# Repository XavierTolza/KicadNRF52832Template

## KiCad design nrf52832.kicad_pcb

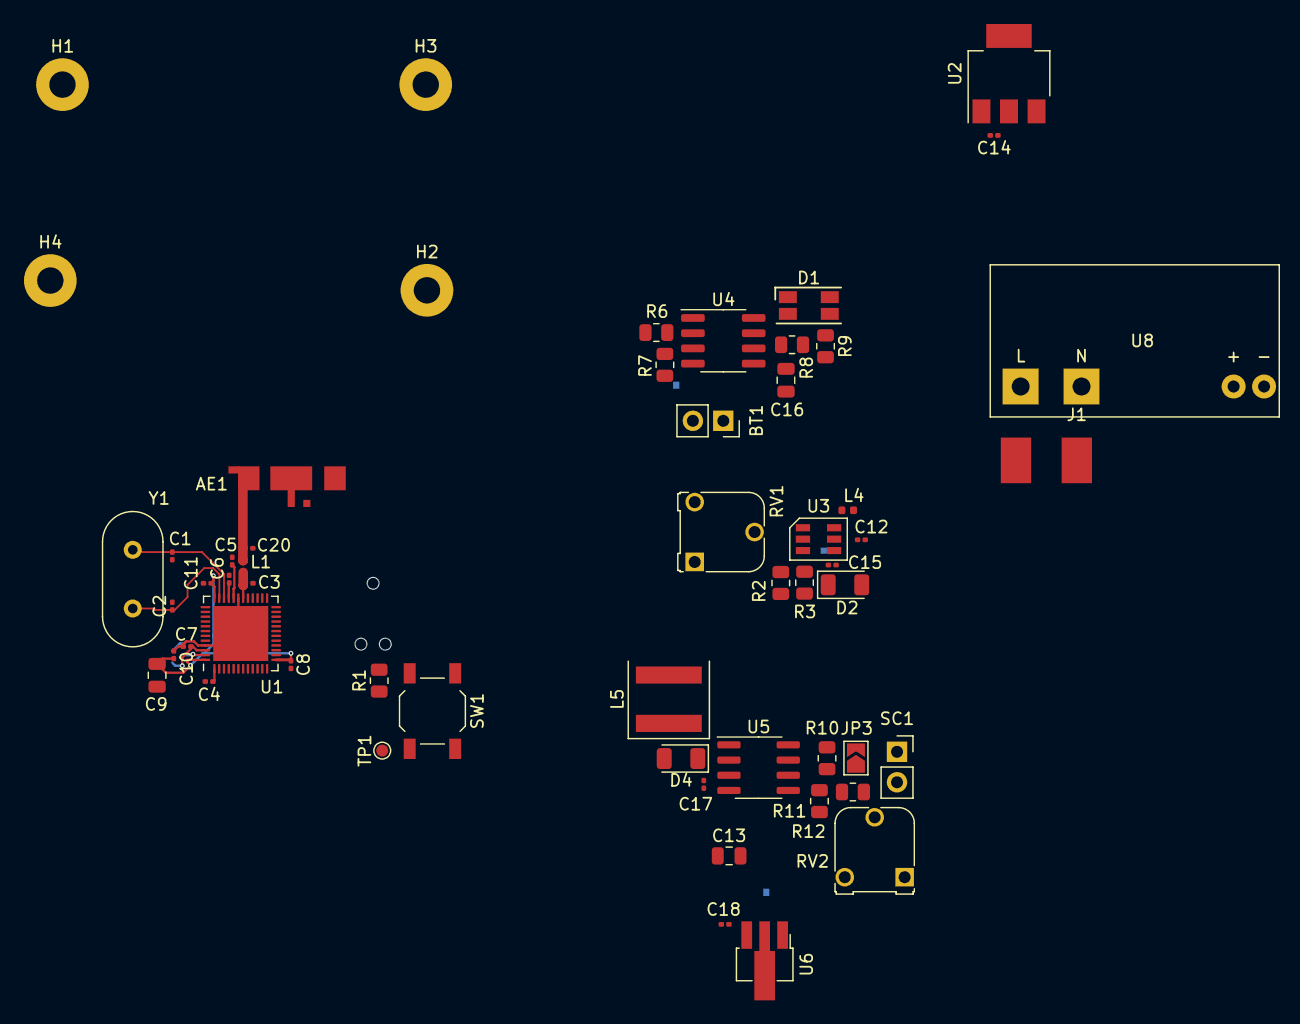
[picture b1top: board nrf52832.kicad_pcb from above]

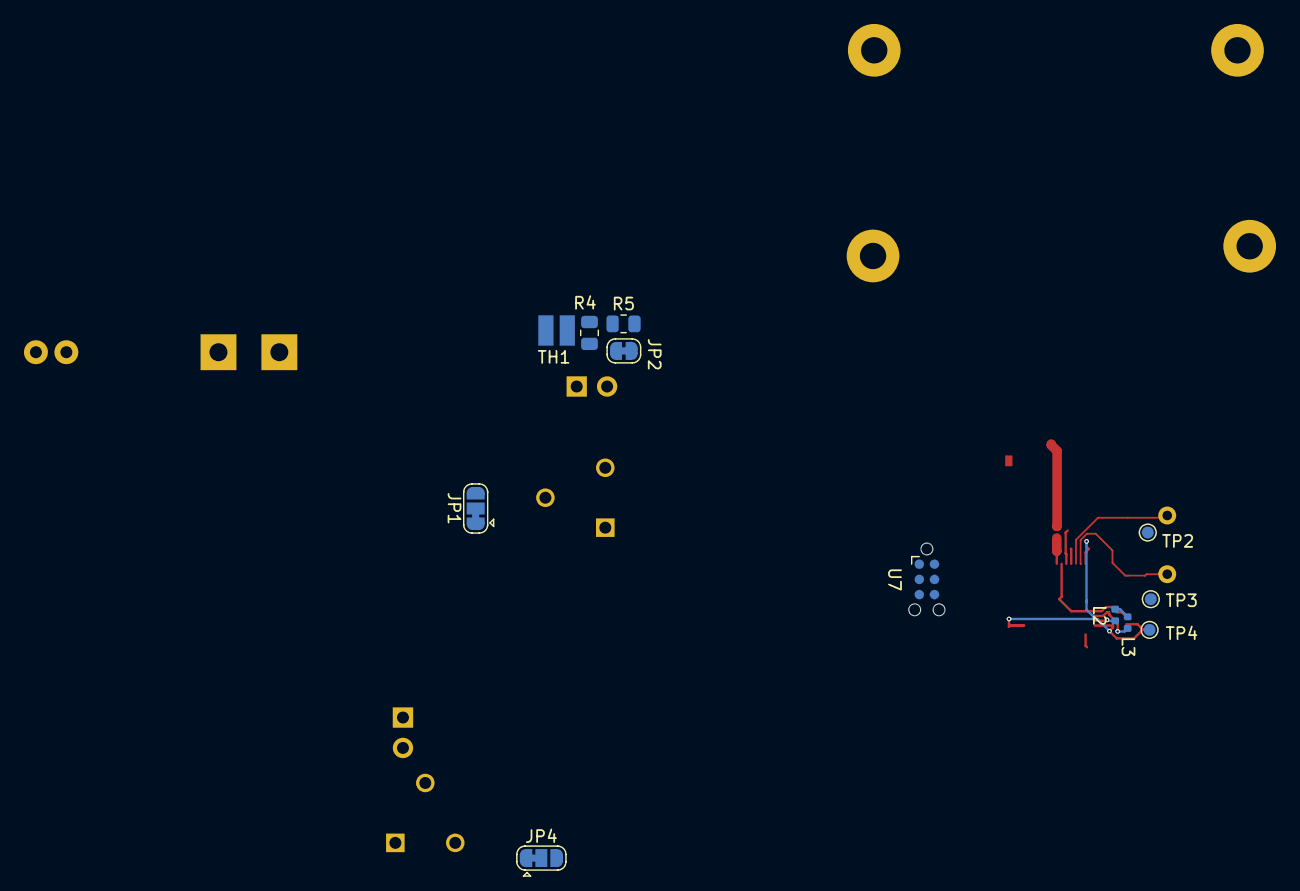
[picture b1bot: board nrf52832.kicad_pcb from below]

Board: 2 copper layers, 68 parts (12 on the bottom side), 39 nets.

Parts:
AE1: Antenna_Dipole; taoglass_LA02_antenna
BT1: bat; PinSocket_1x02_P2.54mm_Vertical
C1, C2: 12pF; C_0201_0603Metric
C3: 0.8pF; C_0201_0603Metric
C4, C8, C10, C11: 100nF; C_0201_0603Metric
C5, C20: NC; C_0201_0603Metric
C6: 100pF; C_0201_0603Metric
C7: 1uF; C_0201_0603Metric
C9: 4.7uF; C_0805_2012Metric
C12, C14, C15: 22uF; C_0201_0603Metric
C13: >=23uF; C_0805_2012Metric
C16: 10uF; C_0805_2012Metric
C17: 280pF; C_0201_0603Metric
C18: 10uF; C_0201_0603Metric
D1: LED_BARG; LED_RGB_1210
D2, D4: D_Schottky; D_1206_3216Metric
H1, H2, H3, H4: Fix; MountingHole_2.2mm_M2_Pad
J1: Conn_01x02; smdpad_01x02_2.54_3.81_2.54
JP1: Boost; SolderJumper-3_P1.3mm_Bridged12_RoundedPad1.0x1.5mm
JP2: TempEN; SolderJumper-2_P1.3mm_Bridged_RoundedPad1.0x1.5mm
JP3: shunt; SolderJumper-2_P1.3mm_Open_TrianglePad1.0x1.5mm
JP4: Reg_select; SolderJumper-3_P1.3mm_Bridged12_RoundedPad1.0x1.5mm
L1: 3.9nH; L_0402_1005Metric
L2: 15nH; L_0402_1005Metric
L3, L4: 10uH; L_0402_1005Metric
L5: >=26uH; L_Coilcraft_XAL60xx_6.36x6.56mm
R1, R6: 10k; R_0805_2012Metric
R2: 37k; R_0805_2012Metric
R3: 5k; R_0805_2012Metric
R4, R5: R; R_0805_2012Metric
R7: 0.4; R_0805_2012Metric
R8, R9, R11: 1k; R_0805_2012Metric
R10: 0.45; R_0805_2012Metric
R12: 3.4k; R_0805_2012Metric
RV1, RV2: R_POT; Potentiometer_Runtron_RM-065_Vertical
SC1: Solar_Cell; PinSocket_1x02_P2.54mm_Vertical
SW1: SW_Push; SW_SPST_TL3342
TH1: NTC; smdpad_01x02_1.27_2.54_0.51
TP1: Reset; TestPoint_Pad_D1.0mm
TP2: XC1; TestPoint_Pad_D1.0mm
TP3: XC2; TestPoint_Pad_D1.0mm
TP4: Vnrf; TestPoint_Pad_D1.0mm
U1: nRF52832-QFxx; QFN-48-1EP_6x6mm_P0.4mm_EP4.6x4.6mm
U2: AMS1117-3.3; SOT-223-3_TabPin2
U3: SX1308
U4: TP4056; SOP-8_3.76x4.96mm_P1.27mm
U5: MC34063AD; SOIC-8_3.9x4.9mm_P1.27mm
U6: HT7127-1-SOT89; SOT-89-3_Handsoldering
U7: TagConnect; Tag-Connect_TC2030-IDC-NL_2x03_P1.27mm_Vertical
U8: WX-DC12003; WX-DC12003_vertical
Y1: 32MHz; Crystal_HC18-U_Vertical

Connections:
+2V8: C18.1, U6.3
+3V3: C14.1, JP1.1, U2.2
+5V: C15.1, D2.1, R2.1, RV1.3
/ANT: AE1.1, C20.1, L1.1
/BB_DC: JP3.2, R10.1, U5.1, U5.7, U5.8
/BB_FB: R11.1, R12.2, RV2.2, U5.5
/BB_SWE: D4.1, L5.1, U5.2
/BB_TC: C17.1, U5.3
/Boost_FB: R2.2, R3.1, RV1.2, U3.3
/Boost_SW: D2.2, L4.2, U3.1
/DCC: L2.1, U1.47
/DEC1: C4.2, U1.1
/DEC2: C5.2, U1.32
/DEC3: C6.2, U1.33
/DEC4: C7.2, L3.2, U1.46
/LPWR_LDO: JP4.2, U6.2
/RF_out: C3.1, L1.2, U1.30
/SWDCLK: U1.25, U7.4
/SWDIO: U1.26, U7.2
/TP4056_Vcc: D1.2, R4.1, R7.2, U4.4, U4.8
/Vbat: BT1.1, C16.1, JP1.3, JP4.3, U4.5
/Vbb_in: JP3.1, R10.2, SC1.1, U5.6
/Vboost_in: C12.1, JP1.2, L4.1, U3.5
/Vnrf: C8.1, C9.1, C10.1, C11.1, R1.1, TP4.1, U1.13, U1.36, U1.48, U7.1
/Vreg: U2.3, U8.3
/nRESET: R1.2, SW1.2, TP1.1, U1.24, U7.3
GND: AE1.2, BT1.2, C1.2, C2.2, C3.2, C4.1, C5.1, C6.1, C7.1, C8.2, C9.2, C10.2, C11.2, C12.2, C13.2, C14.2, C15.2, C16.2, C18.2, C20.2, D4.2, H1.1, H2.1, H3.1, H4.1, JP2.1, R3.2, R5.2, R6.2, R7.1, R11.2, RV1.1, RV2.3, SW1.1, TH1.1, U1.31, U1.45, U1.49, U2.1, U3.2, U4.3, U6.1, U7.5, U8.4
GNDD: C13.1, C17.2, JP4.1, L5.2, R12.1, RV2.1, SC1.2, U5.4
unnamed: C1.1, TP2.1, U1.34, Y1.1
unnamed: C2.1, TP3.1, U1.35, Y1.2
unnamed: D1.3, R9.2
unnamed: D1.4, R8.2
unnamed: J1.1, U8.2
unnamed: J1.2, U8.1
unnamed: JP2.2, R4.2, R5.1, TH1.2, U4.1
unnamed: L2.2, L3.1
unnamed: R6.1, U4.2
unnamed: R8.1, U4.6
unnamed: R9.1, U4.7

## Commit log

2021-10-22 added AC power
2021-10-22 optimized silkscreen
